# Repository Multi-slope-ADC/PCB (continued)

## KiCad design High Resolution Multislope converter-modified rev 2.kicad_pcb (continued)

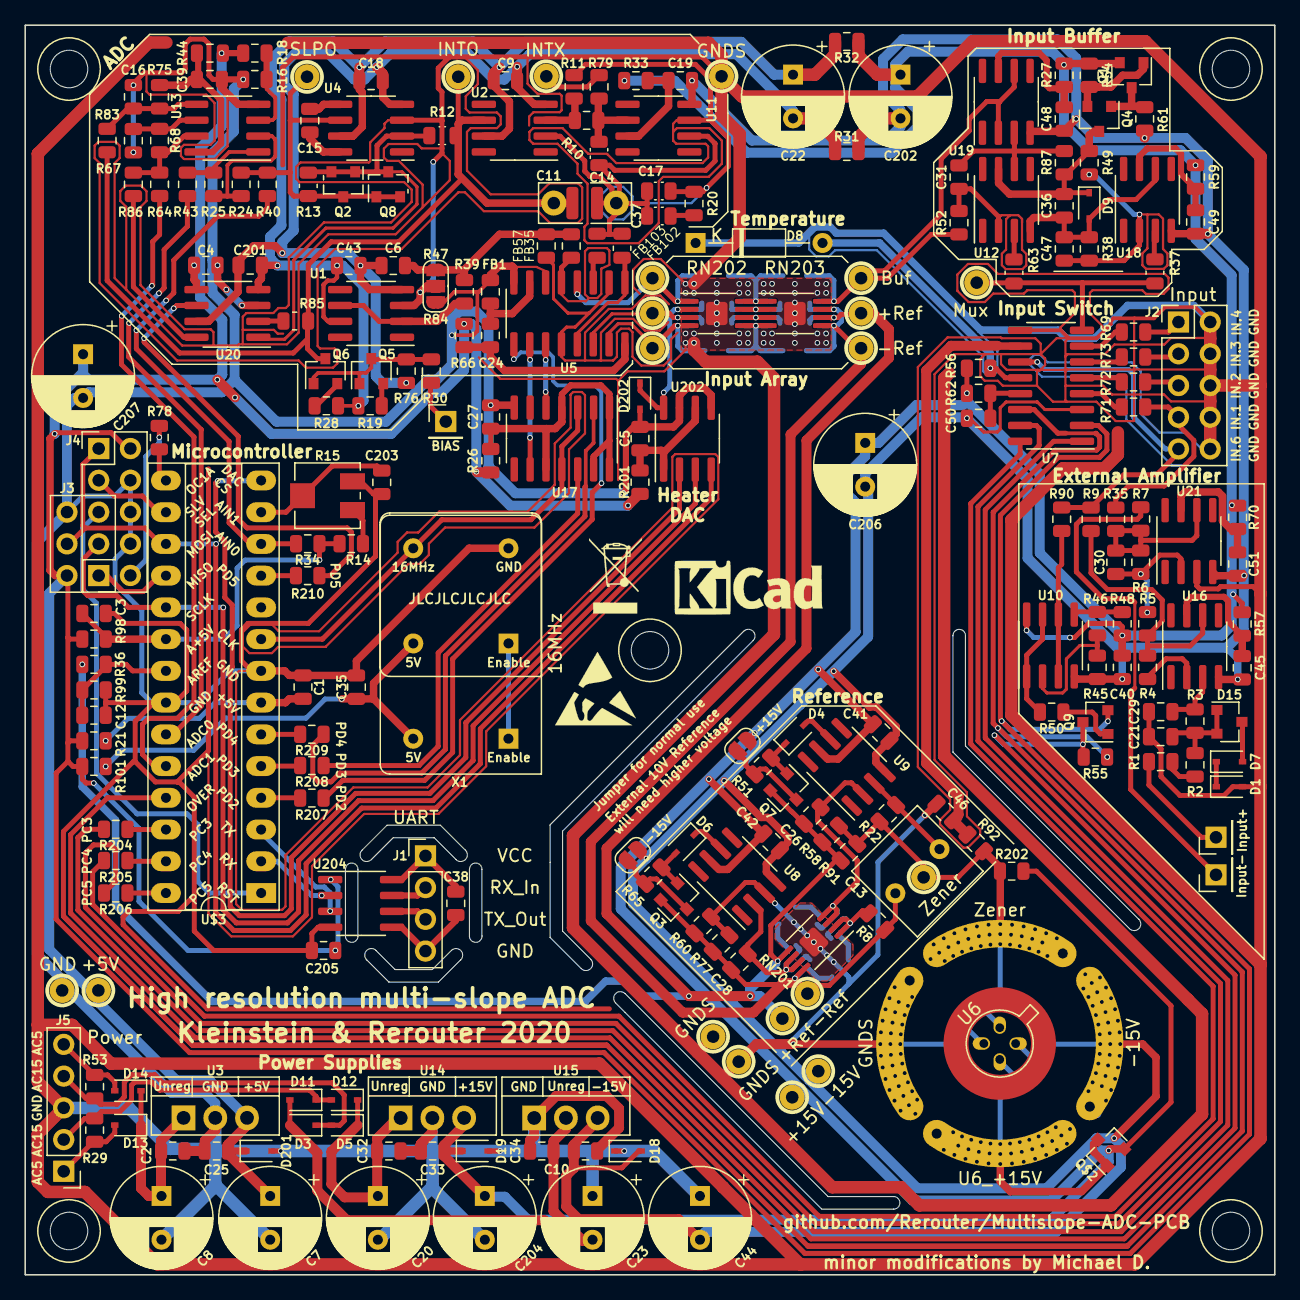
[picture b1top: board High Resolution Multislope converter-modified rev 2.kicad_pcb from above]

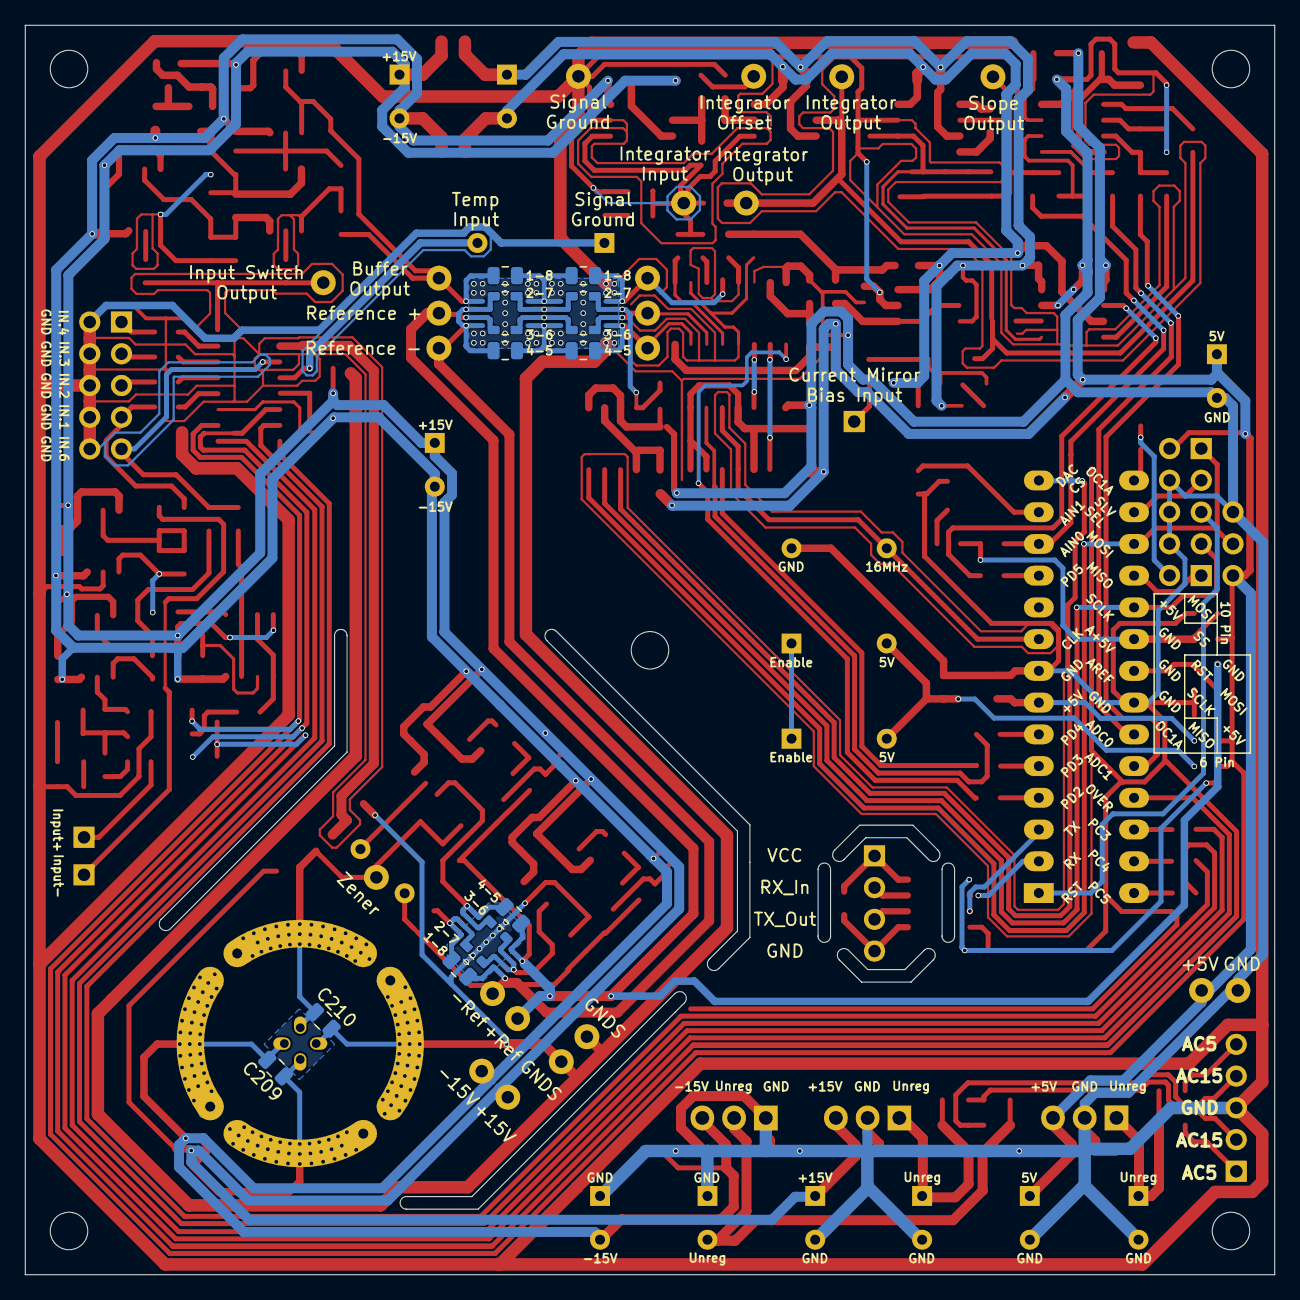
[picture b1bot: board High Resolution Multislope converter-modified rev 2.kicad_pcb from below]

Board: 2 copper layers, 100.0 x 100.0 mm, 257 parts (14 on the bottom side), 154 nets.

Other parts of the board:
1-8, 1-8#2, 2-7, 2-7#2, 2-7#3, 3-6, 3-6#2, 3-6#3, 4-5, 4-5#3: 20K; R_0805_2012Metric
1-8#3, 4-5#2: 10K; R_0805_2012Metric
+5V, +15V: Pin_Header_Straight_1x01_Pitch2.54mm
+Ref: Pin_Header_Straight_1x01_Pitch2.54mm
+Ref#2, +Ref#3: Pin_Header_Straight_1x01_Pitch2.54mm
-15V: Pin_Header_Straight_1x01_Pitch2.54mm
-Ref: Pin_Header_Straight_1x01_Pitch2.54mm
-Ref#2, -Ref#3: Pin_Header_Straight_1x01_Pitch2.54mm
Buf: Pin_Header_Straight_1x01_Pitch2.54mm
Buf#2: Pin_Header_Straight_1x01_Pitch2.54mm
C11#2: 2.2n; C_Rect_L7.2mm_W3.0mm_P5.00mm_FKS2_FKP2_MKS2_MKP2
GND: Pin_Header_Straight_1x01_Pitch2.54mm
GNDS: Pin_Header_Straight_1x01_Pitch2.54mm
GNDS#2, GNDS#3: Pin_Header_Straight_1x01_Pitch2.54mm
INTO: Pin_Header_Straight_1x01_Pitch2.54mm
Mux: Pin_Header_Straight_1x01_Pitch2.54mm
Q8: BC847; SOT-23
R15: 10K; Potentiometer_Vishay_TS53YJ_Vertical
SLPO: Pin_Header_Straight_1x01_Pitch2.54mm
Zener: Pin_Header_Straight_1x01_Pitch2.54mm

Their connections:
+5V: +5V.1; also elsewhere on the board
+15V: +15V.1; also elsewhere on the board
-15V: -15V.1; also elsewhere on the board
/+Ref_In: 3-6.1, +Ref#2.1; also elsewhere on the board
/-Ref_In: 4-5.1, -Ref#2.1; also elsewhere on the board
/AIN1: R15.2; also elsewhere on the board
/Buffer_Output: 1-8#2.2, Buf#2.1; also elsewhere on the board
/Heater_Setpoint: 2-7.1; also elsewhere on the board
/Integrator_Input: C11#2.1; also elsewhere on the board
/Integrator_Output: C11#2.2, INTO.1; also elsewhere on the board
/LM399_Zener_Voltage: Zener.1; also elsewhere on the board
/Mux_Output: Mux.1; also elsewhere on the board
/Ref_+14V: 3-6#2.2, 4-5#2.2, +Ref.1, +Ref#3.1; also elsewhere on the board
/Ref_-13.4V: 1-8#3.2, 2-7#3.2, 4-5#3.2, -Ref.1, -Ref#3.1; also elsewhere on the board
/Sig_In: 1-8.1, Buf.1; also elsewhere on the board
/Slope_Input: Q8.3; also elsewhere on the board
/Slope_Output: Q8.1, Q8.2, SLPO.1; also elsewhere on the board
/U8_FB: 2-7#2.2, 3-6#3.2; also elsewhere on the board
/U9_FB: 3-6#3.1, 4-5#2.1; also elsewhere on the board
GND: GND.1, R15.1; also elsewhere on the board
GNDS: GNDS.1, GNDS#2.1, GNDS#3.1; also elsewhere on the board
unnamed 138: 1-8#3.1, 2-7#2.1; also elsewhere on the board
unnamed 139: R15.3; also elsewhere on the board
unnamed 160: 4-5.2, 4-5#3.1; also elsewhere on the board
unnamed 161: 3-6.2, 3-6#2.1; also elsewhere on the board
unnamed 162: 2-7.2, 2-7#3.1; also elsewhere on the board
unnamed 163: 1-8.2, 1-8#2.1; also elsewhere on the board

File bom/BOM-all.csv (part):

"Reference","Value","Footprint","Quantity","DNP","Manufacturer","Manufacturer Part Number","Datasheet","Jumper State","Assembly note"
"C1","100n","Capacitor_SMD:C_0805_2012Metric","1","","KYOCERA AVX","08055C104KAT2A","https://datasheets.kyocera-avx.com/X7RDielectric.pdf","",""
"C2","100n","Capacitor_SMD:C_0805_2012Metric","1","","KYOCERA AVX","08055C104KAT2A","https://datasheets.kyocera-avx.com/X7RDielectric.pdf","",""
"C3","100n","Capacitor_SMD:C_0805_2012Metric","1","","KYOCERA AVX","08055C104KAT2A","https://datasheets.kyocera-avx.com/X7RDielectric.pdf","",""
"C4","100n","Capacitor_SMD:C_0805_2012Metric","1","","KYOCERA AVX","08055C104KAT2A","https://datasheets.kyocera-avx.com/X7RDielectric.pdf","",""
"C5","100n","Capacitor_SMD:C_0805_2012Metric","1","","KYOCERA AVX","08055C104KAT2A","https://datasheets.kyocera-avx.com/X7RDielectric.pdf","",""
"C6","2.2u","Capacitor_SMD:C_0805_2012Metric","1","DNP","Samsung Electro-Mechanics","CL21B225KAFNNNE","https://product.samsungsem.com/mlcc/CL21B225KAFNNN.do","",""
"C7","100u","Capacitor_THT:CP_Radial_D8.0mm_P3.50mm","1","","Panasonic","EEU-EB1J101","https://industrial.panasonic.com/ww/products/pt/aluminum-cap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","",""
"C8","100u","Capacitor_THT:CP_Radial_D8.0mm_P3.50mm","1","","Panasonic","EEU-EB1J101","https://industrial.panasonic.com/ww/products/pt/aluminum-cap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","",""
"C9","100n","Capacitor_SMD:C_0805_2012Metric","1","","KYOCERA AVX","08055C104KAT2A","https://datasheets.kyocera-avx.com/X7RDielectric.pdf","",""
"C10","100n","Capacitor_SMD:C_0805_2012Metric","1","","KYOCERA AVX","08055C104KAT2A","https://datasheets.kyocera-avx.com/X7RDielectric.pdf","",""
"C11","2.2n","Capacitor_SMD:C_0805_2012Metric","1","","TDK","C2012C0G1H222J085AA","https://product.tdk.com/en/search/capacitor/ceramic/mlcc/inf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","",""
"C12","100n","Capacitor_SMD:C_0805_2012Metric","1","","KYOCERA AVX","08055C104KAT2A","https://datasheets.kyocera-avx.com/X7RDielectric.pdf","",""
"C13","4.7u","Capacitor_THT:C_Rect_L7.2mm_W7.2mm_P5.00mm_FKS2_FKP2_MKS2_MKP2","1","","WIMA","MKS2C044701M00KSSD","https://www.wima.de/wp-content/uploads/media/e_WIMA_MKS_2.pdf","",""
"C14","220p","Capacitor_SMD:C_0805_2012Metric","1","","Samsung Electro-Mechanics","CL21C221JBANNNC","https://product.samsungsem.com/mlcc/CL21C221JBANNN.do","",""
"C15","22p","Capacitor_SMD:C_0805_2012Metric","1","","Samsung Electro-Mechanics","CL21C220JBANNNC","https://product.samsungsem.com/mlcc/CL21C220JBANNN.do","","Original assembly: first of two parallel 22pF parts at C15; second part C211. Total 44pF, user confirmed."
"C16","10n","Capacitor_SMD:C_0805_2012Metric","1","","TDK","CGA4C2C0G1H103J060AA","https://product.tdk.com/en/search/capacitor/ceramic/mlcc/inf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","",""
"C17","330p","Capacitor_SMD:C_0805_2012Metric","1","","KEMET","C0805C331J5GACTU","https://content.kemet.com/datasheets/KEM_C1003_C0G_SMD.pdf","",""
"C18","100n","Capacitor_SMD:C_0805_2012Metric","1","","KYOCERA AVX","08055C104KAT2A","https://datasheets.kyocera-avx.com/X7RDielectric.pdf","",""
"C19","100n","Capacitor_SMD:C_0805_2012Metric","1","","KYOCERA AVX","08055C104KAT2A","https://datasheets.kyocera-avx.com/X7RDielectric.pdf","",""
"C20","100u","Capacitor_THT:CP_Radial_D8.0mm_P3.50mm","1","","Panasonic","EEU-EB1J101","https://industrial.panasonic.com/ww/products/pt/aluminum-cap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","",""
"C21","220p","Capacitor_SMD:C_0805_2012Metric","1","","Samsung Electro-Mechanics","CL21C221JBANNNC","https://product.samsungsem.com/mlcc/CL21C221JBANNN.do","",""
"C22","100u","Capacitor_THT:CP_Radial_D8.0mm_P3.50mm","1","","Panasonic","EEU-EB1J101","https://industrial.panasonic.com/ww/products/pt/aluminum-cap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","",""
"C23","100u","Capacitor_THT:CP_Radial_D8.0mm_P3.50mm","1","","Panasonic","EEU-EB1J101","https://industrial.panasonic.com/ww/products/pt/aluminum-cap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","",""
"C24","100n","Capacitor_SMD:C_0805_2012Metric","1","","KYOCERA AVX","08055C104KAT2A","https://datasheets.kyocera-avx.com/X7RDielectric.pdf","",""
"C25","100n","Capacitor_SMD:C_0805_2012Metric","1","","KYOCERA AVX","08055C104KAT2A","https://datasheets.kyocera-avx.com/X7RDielectric.pdf","",""
"C26","47n","Capacitor_SMD:C_0805_2012Metric","1","","KEMET","C0805C473K3GECAUTO","https://content.kemet.com/datasheets/KEM_C1022_C0G_AUTO_SMD.pdf","",""
"C27","100n","Capacitor_SMD:C_0805_2012Metric","1","","KYOCERA AVX","08055C104KAT2A","https://datasheets.kyocera-avx.com/X7RDielectric.pdf","",""
"C28","47n","Capacitor_SMD:C_0805_2012Metric","1","","KEMET","C0805C473K3GECAUTO","https://content.kemet.com/datasheets/KEM_C1022_C0G_AUTO_SMD.pdf","",""
"C29","220p","Capacitor_SMD:C_0805_2012Metric","1","","Samsung Electro-Mechanics","CL21C221JBANNNC","https://product.samsungsem.com/mlcc/CL21C221JBANNN.do","",""
"C30","1n","Capacitor_SMD:C_0805_2012Metric","1","","Wurth Elektronik","885012007063","https://www.we-online.com/components/products/datasheet/8850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","",""
"C31","100n","Capacitor_SMD:C_0805_2012Metric","1","","KEMET","C0805C473K3GECAUTO","https://content.kemet.com/datasheets/KEM_C1022_C0G_AUTO_SMD.pdf","",""
"C32","100n","Capacitor_SMD:C_0805_2012Metric","1","","KYOCERA AVX","08055C104KAT2A","https://datasheets.kyocera-avx.com/X7RDielectric.pdf","",""
"C33","100n","Capacitor_SMD:C_0805_2012Metric","1","","KYOCERA AVX","08055C104KAT2A","https://datasheets.kyocera-avx.com/X7RDielectric.pdf","",""
"C34","100n","Capacitor_SMD:C_0805_2012Metric","1","","KYOCERA AVX","08055C104KAT2A","https://datasheets.kyocera-avx.com/X7RDielectric.pdf","",""
"C35","100n","Capacitor_SMD:C_0805_2012Metric","1","","KYOCERA AVX","08055C104KAT2A","https://datasheets.kyocera-avx.com/X7RDielectric.pdf","",""
"C36","100n","Capacitor_SMD:C_0805_2012Metric","1","","KYOCERA AVX","08055C104KAT2A","https://datasheets.kyocera-avx.com/X7RDielectric.pdf","",""
"C37","1n","Capacitor_SMD:C_0805_2012Metric","1","DNP","Wurth Elektronik","885012007063","https://www.we-online.com/components/products/datasheet/8850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","",""
"C38","100n","Capacitor_SMD:C_0805_2012Metric","1","","KYOCERA AVX","08055C104KAT2A","https://datasheets.kyocera-avx.com/X7RDielectric.pdf","",""
"C39","100n","Capacitor_SMD:C_0805_2012Metric","1","","KYOCERA AVX","08055C104KAT2A","https://datasheets.kyocera-avx.com/X7RDielectric.pdf","",""
"C40","100n","Capacitor_SMD:C_0805_2012Metric","1","","KYOCERA AVX","08055C104KAT2A","https://datasheets.kyocera-avx.com/X7RDielectric.pdf","",""
"C41","100n","Capacitor_SMD:C_0805_2012Metric","1","","KYOCERA AVX","08055C104KAT2A","https://datasheets.kyocera-avx.com/X7RDielectric.pdf","",""
"C42","100n","Capacitor_SMD:C_0805_2012Metric","1","","KYOCERA AVX","08055C104KAT2A","https://datasheets.kyocera-avx.com/X7RDielectric.pdf","",""
"C43","100n","Capacitor_SMD:C_0805_2012Metric","1","","KYOCERA AVX","08055C104KAT2A","https://datasheets.kyocera-avx.com/X7RDielectric.pdf","",""
"C44","100u","Capacitor_THT:CP_Radial_D8.0mm_P3.50mm","1","","Panasonic","EEU-EB1J101","https://industrial.panasonic.com/ww/products/pt/aluminum-cap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","",""
"C45","100n","Capacitor_SMD:C_0805_2012Metric","1","","KYOCERA AVX","08055C104KAT2A","https://datasheets.kyocera-avx.com/X7RDielectric.pdf","",""
"C46","47n","Capacitor_SMD:C_0805_2012Metric","1","","KEMET","C0805C473K3GECAUTO","https://content.kemet.com/datasheets/KEM_C1022_C0G_AUTO_SMD.pdf","",""
"C47","10n","Capacitor_SMD:C_0805_2012Metric","1","","TDK","CGA4C2C0G1H103J060AA","https://product.tdk.com/en/search/capacitor/ceramic/mlcc/inf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","",""
"C48","100n","Capacitor_SMD:C_0805_2012Metric","1","","KYOCERA AVX","08055C104KAT2A","https://datasheets.kyocera-avx.com/X7RDielectric.pdf","",""
"C49","100n","Capacitor_SMD:C_0805_2012Metric","1","","KYOCERA AVX","08055C104KAT2A","https://datasheets.kyocera-avx.com/X7RDielectric.pdf","",""
"C50","100n","Capacitor_SMD:C_0805_2012Metric","1","","KYOCERA AVX","08055C104KAT2A","https://datasheets.kyocera-avx.com/X7RDielectric.pdf","",""
"C51","100n","Capacitor_SMD:C_0805_2012Metric","1","","KYOCERA AVX","08055C104KAT2A","https://datasheets.kyocera-avx.com/X7RDielectric.pdf","",""
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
